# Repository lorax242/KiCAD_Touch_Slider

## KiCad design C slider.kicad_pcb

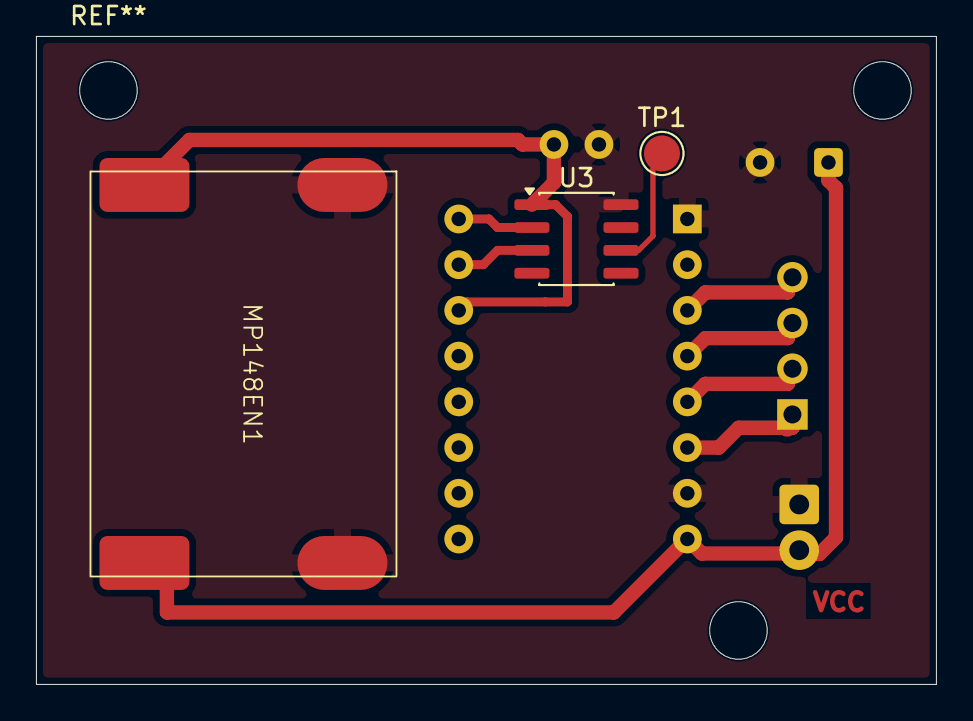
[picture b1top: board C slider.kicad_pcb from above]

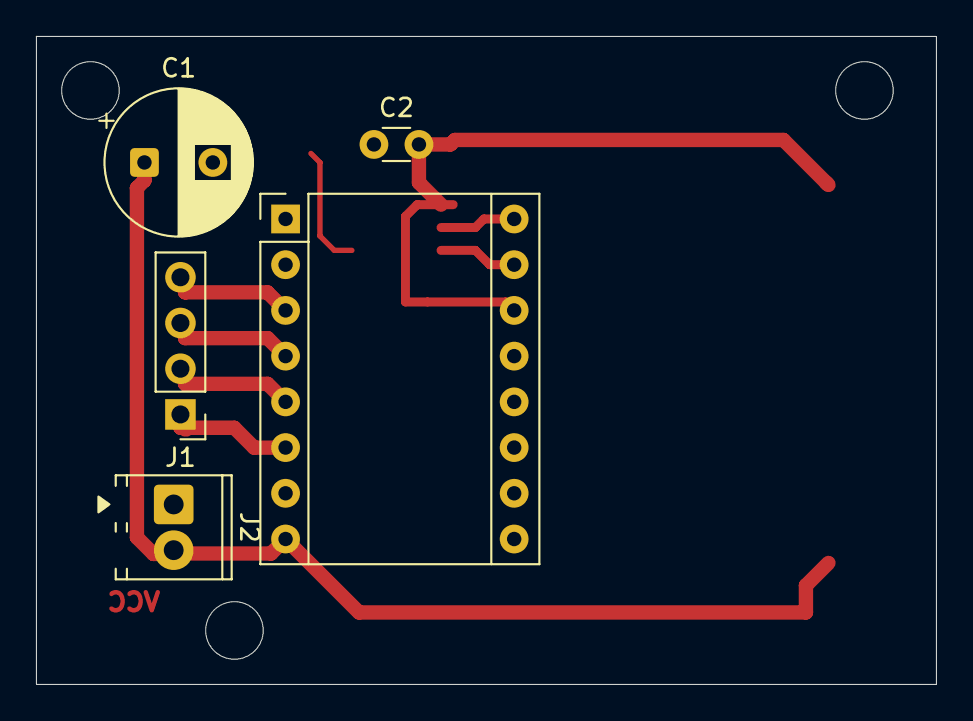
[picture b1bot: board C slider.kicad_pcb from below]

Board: 2 copper layers, 50.0 x 36.0 mm, 8 parts (5 on the bottom side), 10 nets.

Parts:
A1: Pololu_Breakout_DRV8825; Pololu_Breakout-16_15.2x20.3mm
C1: 100u/35V; CP_Radial_D8.0mm_P3.80mm
C2: 100n; C_Disc_D3.0mm_W1.6mm_P2.50mm
J1: Conn_01x04_Pin; PinHeader_1x04_P2.54mm_Vertical
J2: Conn_01x02_Pin; TerminalBlock_Phoenix_MPT-0,5-2-2.54_1x02_P2.54mm_Horizontal
MP148EN1: 12/3,3V; MP148EN1
TP1: TestPoint; TestPoint_Pad_D2.0mm
U3: ATtiny412-SS; SOIC-8_3.9x4.9mm_P1.27mm

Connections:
+12V: A1.8 (VMOT), C1.1, J2.2, MP148EN1.4 (V_IN)
GND: A1.1 (GND), A1.7 (GND), C1.2, C2.1, J2.1, MP148EN1.1 (GND), MP148EN1.2 (GND), U3.8 (GND)
unnamed: A1.4 (A1), J1.3
unnamed: A1.3 (A2), J1.4
unnamed: A1.5 (B1), J1.2
unnamed: A1.6 (B2), J1.1
unnamed: A1.16 (DIR), U3.2 (PA6)
unnamed: A1.12 (M2), A1.13 (~RST), A1.14 (~SLP), C2.2, MP148EN1.3 (V_OUT), U3.1 (VCC)
unnamed: A1.15 (STEP), U3.3 (PA7)
unnamed: TP1.1 (1_1), U3.6 (~RESET/PA0)
